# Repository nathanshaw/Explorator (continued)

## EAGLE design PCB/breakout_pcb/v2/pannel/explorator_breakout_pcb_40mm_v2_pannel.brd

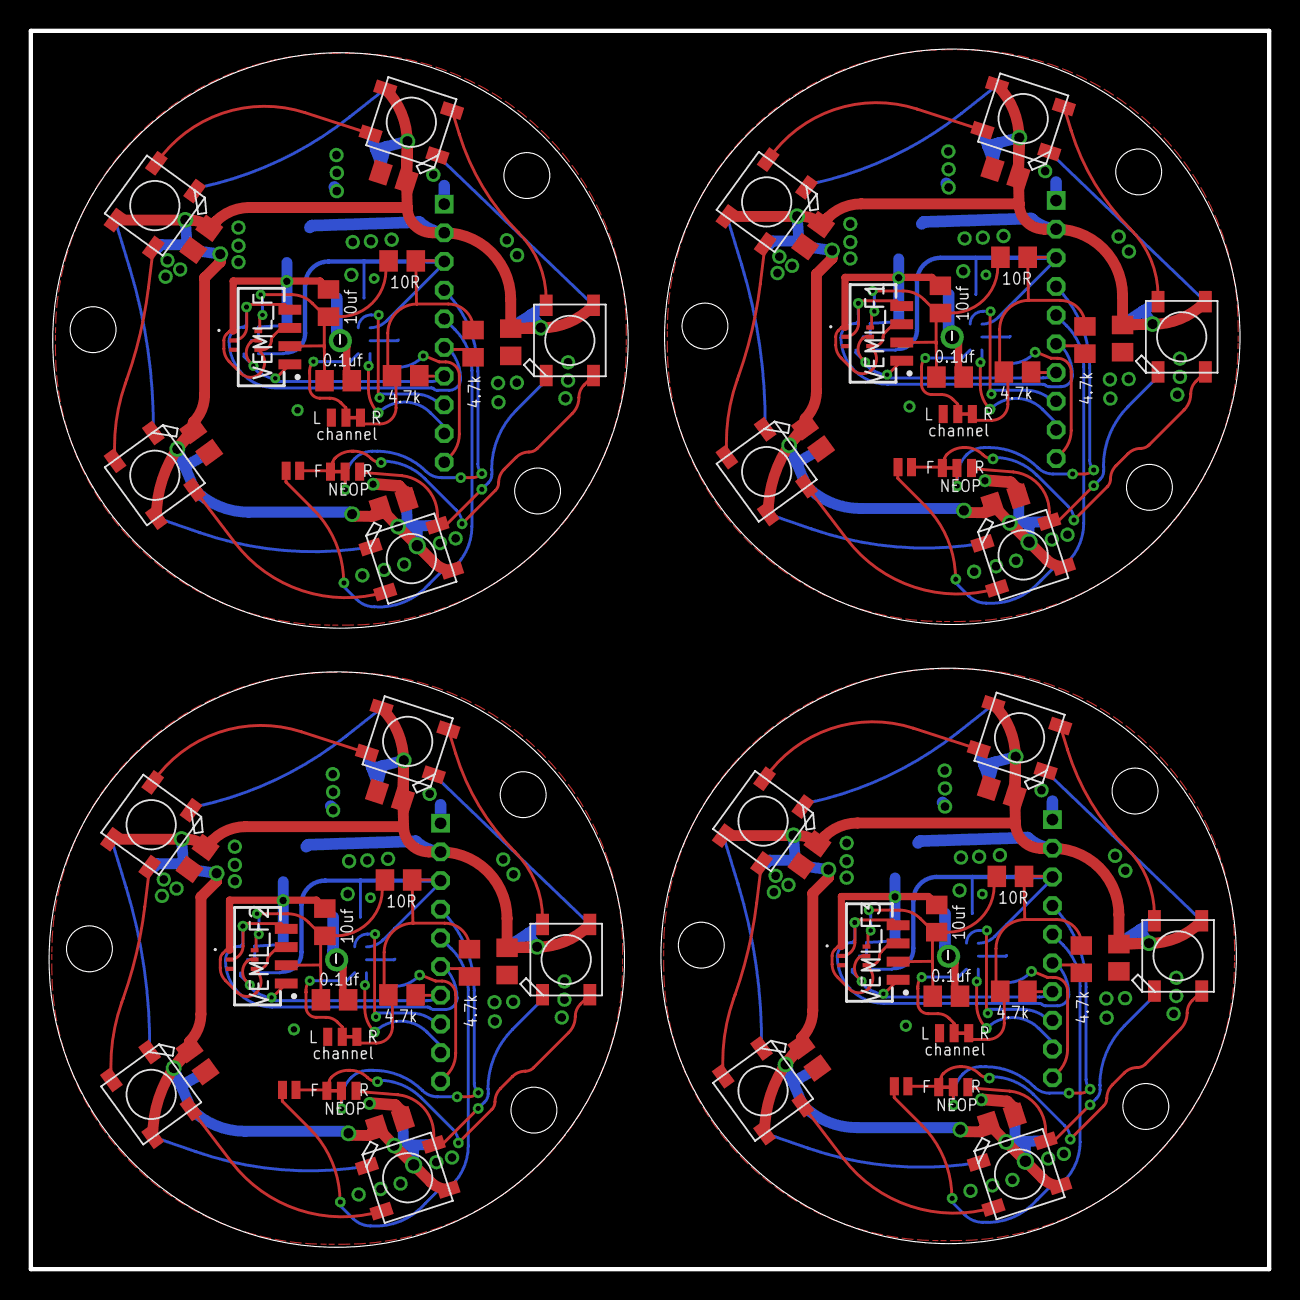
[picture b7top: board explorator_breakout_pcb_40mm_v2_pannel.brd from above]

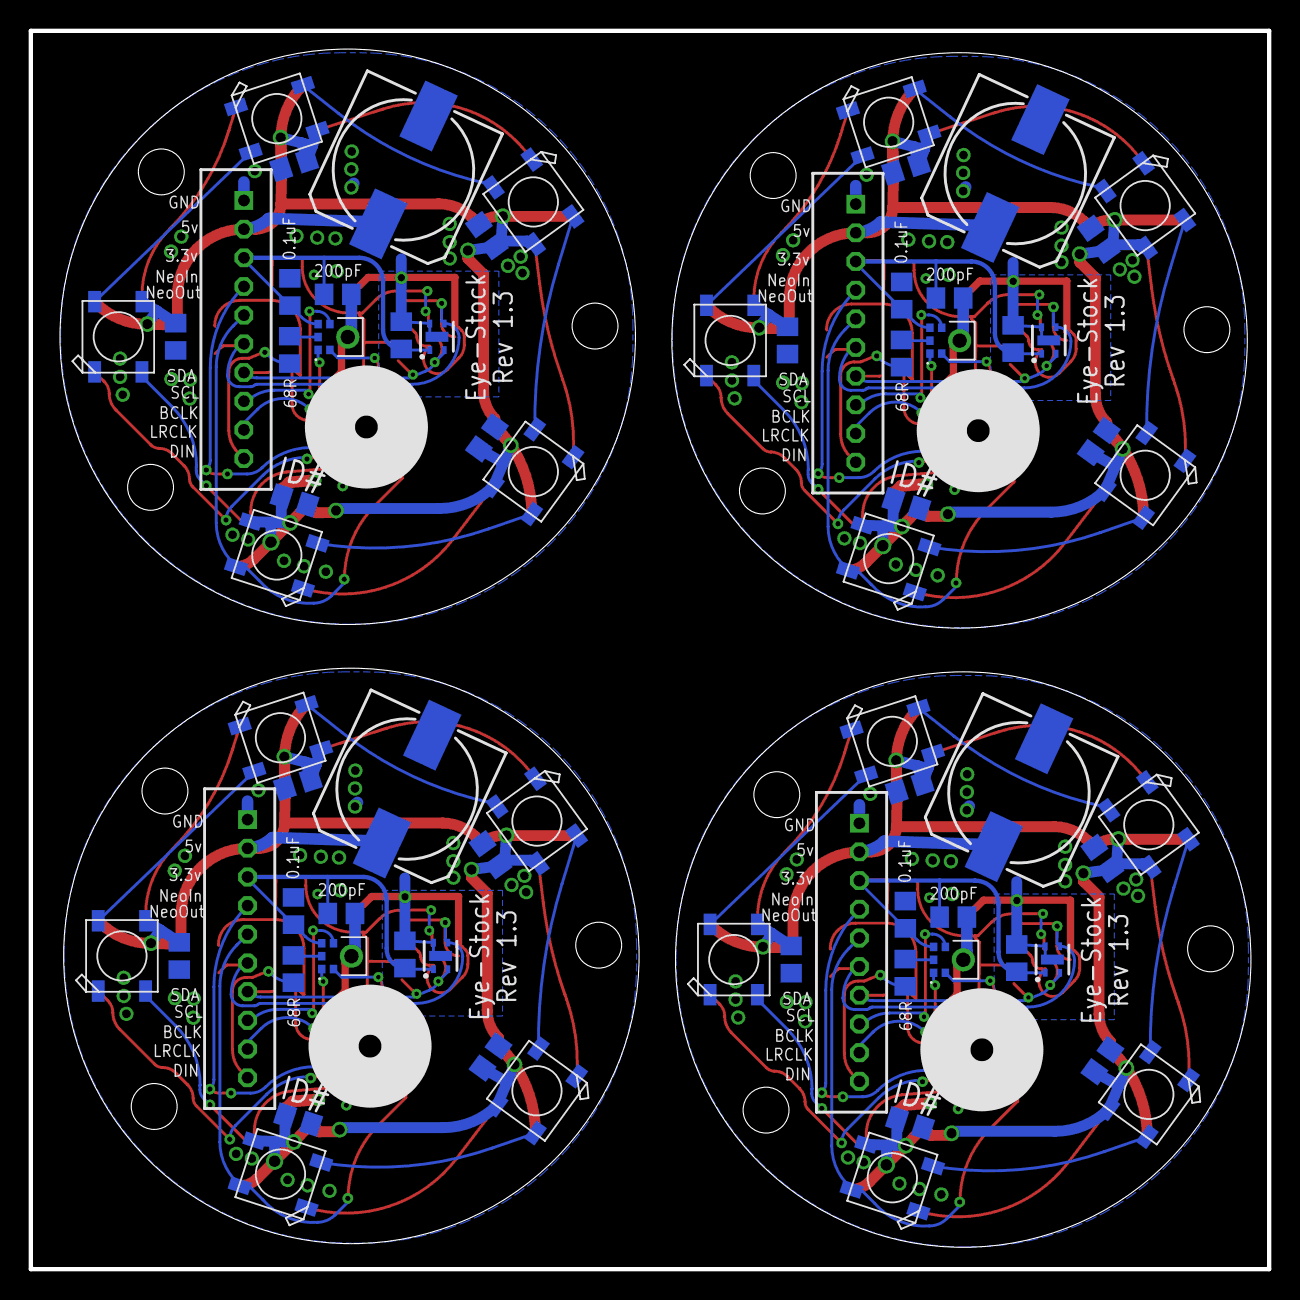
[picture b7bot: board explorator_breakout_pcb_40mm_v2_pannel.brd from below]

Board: 2 copper layers, 86.4 x 86.4 mm, 152 parts (72 on the bottom side), 92 nets.

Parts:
C1, C5, C13, C19: 0.1uf; C0805
C2, C7, C8, C11, C15, C17, C21, C23: 0.1uF; C0805
C3, C12, C18, C24: 1mF; 153CLV-1012
C4, C6, C14, C20: 10uf; C0805
C9, C10, C16, C22: 200pF; C0805
JP1, JP2, JP3, JP5, JP7, JP8, JP10, JP11: JUMPER-SMT-3POS_NC_ONE; SMT-JUMPER_3_1-NC_TRACE_NO-SILK
JP4, JP6, JP9, JP12: JUMPER-SMT-2POS; SMT-JUMPER_2_NO_NO-SILK
MK_REAR, MK_REAR1, MK_REAR2, MK_REAR3: SPH-IMPROVED; MIC_SPH0645LM4H-B_LARGER_RING
NC1, NC2, NC3, NC4, NC5, NC6, NC7, NC8, NC9, NC10, NC11, NC12, NC13, NC14, NC15, NC16, NC17, NC18, NC19, NC20, NC21, NC22, NC23, NC24, NC25, NC26, NC27, NC28, NC29, NC30, NC31, NC32, NC33, NC34, NC35, NC36, NC37, NC38, NC39, NC40: 0.1uf; C0805
NEO_01, NEO_02, NEO_03, NEO_04, NEO_05, NEO_06, NEO_07, NEO_08, NEO_09, NEO_10, NEO_11, NEO_12, NEO_13, NEO_14, NEO_15, NEO_16, NEO_17, NEO_18, NEO_19, NEO_20, NEO_21, NEO_22, NEO_23, NEO_24, NEO_25, NEO_26, NEO_27, NEO_28, NEO_29, NEO_30, NEO_31, NEO_32, NEO_33, NEO_34, NEO_35, NEO_36, NEO_37, NEO_38, NEO_39, NEO_40: WS2812; WS2812B
P1, P2, P3, P4: B10B-PH-K
R1, R3, R8, R12: 10R; R0805
R2, R4, R5, R6, R9, R10, R13, R14: 4.7k; R0805
R7, R11, R15, R16: 68R; R0805
U1, U3, U5, U7: SHTC3
U2, U4, U6, U8: VEML6030-GS15; VISHAY_VEML6030_2X2X0.87
VEML_F, VEML_F1, VEML_F2, VEML_F3: VEML7700-TT; VEML7700

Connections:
3.3V: C2.1, C8.1, C9.1, JP3.3, MK_REAR.5, P1.3, R3.2, R5.2, R6.2, U1.1
3.3V1: C7.1, C10.1, C11.1, JP5.3, MK_REAR1.5, P2.3, R1.2, R2.2, R4.2, U3.1
3.3V2: C15.1, C16.1, C17.1, JP8.3, MK_REAR2.5, P3.3, R8.2, R9.2, R10.2, U5.1
3.3V3: C21.1, C22.1, C23.1, JP11.3, MK_REAR3.5, P4.3, R12.2, R13.2, R14.2, U7.1
5V: C3.+, NC1.1, NC2.1, NC3.1, NC4.1, NC5.1, NC6.1, NC7.1, NC8.1, NC9.1, NC10.1, NEO_01.1-VDD, NEO_02.1-VDD, NEO_03.1-VDD, NEO_04.1-VDD, NEO_05.1-VDD, NEO_06.1-VDD, NEO_07.1-VDD, NEO_08.1-VDD, NEO_09.1-VDD, NEO_10.1-VDD, P1.2
5V1: C12.+, NC11.1, NC12.1, NC13.1, NC14.1, NC15.1, NC16.1, NC17.1, NC18.1, NC19.1, NC20.1, NEO_11.1-VDD, NEO_12.1-VDD, NEO_13.1-VDD, NEO_14.1-VDD, NEO_15.1-VDD, NEO_16.1-VDD, NEO_17.1-VDD, NEO_18.1-VDD, NEO_19.1-VDD, NEO_20.1-VDD, P2.2
5V2: C18.+, NC21.1, NC22.1, NC23.1, NC24.1, NC25.1, NC26.1, NC27.1, NC28.1, NC29.1, NC30.1, NEO_21.1-VDD, NEO_22.1-VDD, NEO_23.1-VDD, NEO_24.1-VDD, NEO_25.1-VDD, NEO_26.1-VDD, NEO_27.1-VDD, NEO_28.1-VDD, NEO_29.1-VDD, NEO_30.1-VDD, P3.2
5V3: C24.+, NC31.1, NC32.1, NC33.1, NC34.1, NC35.1, NC36.1, NC37.1, NC38.1, NC39.1, NC40.1, NEO_31.1-VDD, NEO_32.1-VDD, NEO_33.1-VDD, NEO_34.1-VDD, NEO_35.1-VDD, NEO_36.1-VDD, NEO_37.1-VDD, NEO_38.1-VDD, NEO_39.1-VDD, NEO_40.1-VDD, P4.2
BCLK: MK_REAR.4, P1.8
BCLK1: MK_REAR1.4, P2.8
BCLK2: MK_REAR2.4, P3.8
BCLK3: MK_REAR3.4, P4.8
DIN: P1.10, R15.2
DIN1: P2.10, R7.2
DIN2: P3.10, R11.2
DIN3: P4.10, R16.2
GND: C1.2, C2.2, C3.-, C4.2, C8.2, C9.2, JP3.1, MK_REAR.P$1, NC1.2, NC2.2, NC3.2, NC4.2, NC5.2, NC6.2, NC7.2, NC8.2, NC9.2, NC10.2, NEO_01.3-GND, NEO_02.3-GND, NEO_03.3-GND, NEO_04.3-GND, NEO_05.3-GND, NEO_06.3-GND, NEO_07.3-GND, NEO_08.3-GND, NEO_09.3-GND, NEO_10.3-GND, P1.1, U1.4, U1.5, U2.1, U2.4, VEML_F.3
GND1: C5.2, C6.2, C7.2, C10.2, C11.2, C12.-, JP5.1, MK_REAR1.P$1, NC11.2, NC12.2, NC13.2, NC14.2, NC15.2, NC16.2, NC17.2, NC18.2, NC19.2, NC20.2, NEO_11.3-GND, NEO_12.3-GND, NEO_13.3-GND, NEO_14.3-GND, NEO_15.3-GND, NEO_16.3-GND, NEO_17.3-GND, NEO_18.3-GND, NEO_19.3-GND, NEO_20.3-GND, P2.1, U3.4, U3.5, U4.1, U4.4, VEML_F1.3
GND2: C13.2, C14.2, C15.2, C16.2, C17.2, C18.-, JP8.1, MK_REAR2.P$1, NC21.2, NC22.2, NC23.2, NC24.2, NC25.2, NC26.2, NC27.2, NC28.2, NC29.2, NC30.2, NEO_21.3-GND, NEO_22.3-GND, NEO_23.3-GND, NEO_24.3-GND, NEO_25.3-GND, NEO_26.3-GND, NEO_27.3-GND, NEO_28.3-GND, NEO_29.3-GND, NEO_30.3-GND, P3.1, U5.4, U5.5, U6.1, U6.4, VEML_F2.3
GND3: C19.2, C20.2, C21.2, C22.2, C23.2, C24.-, JP11.1, MK_REAR3.P$1, NC31.2, NC32.2, NC33.2, NC34.2, NC35.2, NC36.2, NC37.2, NC38.2, NC39.2, NC40.2, NEO_31.3-GND, NEO_32.3-GND, NEO_33.3-GND, NEO_34.3-GND, NEO_35.3-GND, NEO_36.3-GND, NEO_37.3-GND, NEO_38.3-GND, NEO_39.3-GND, NEO_40.3-GND, P4.1, U7.4, U7.5, U8.1, U8.4, VEML_F3.3
LRCLK: MK_REAR.1, P1.9
LRCLK1: MK_REAR1.1, P2.9
LRCLK2: MK_REAR2.1, P3.9
LRCLK3: MK_REAR3.1, P4.9
unnamed: C1.1, C4.1, R3.1, U2.6, VEML_F.2
unnamed: JP1.1, NEO_05.2-DOUT, NEO_06.4-DIN
unnamed: NEO_11.2-DOUT, NEO_12.4-DIN
unnamed: NEO_02.2-DOUT, NEO_03.4-DIN
unnamed: NEO_09.2-DOUT, NEO_10.4-DIN
unnamed: JP3.2, MK_REAR.2
unnamed: NEO_07.2-DOUT, NEO_08.4-DIN
unnamed: NEO_04.2-DOUT, NEO_05.4-DIN
unnamed: NEO_08.2-DOUT, NEO_09.4-DIN
unnamed: NEO_03.2-DOUT, NEO_04.4-DIN
unnamed: NEO_14.2-DOUT, NEO_15.4-DIN
unnamed: C5.1, C6.1, R1.1, U4.6, VEML_F1.2
unnamed: NEO_11.4-DIN, NEO_15.2-DOUT
unnamed: MK_REAR1.6, R7.1
unnamed: JP5.2, MK_REAR1.2
unnamed: NEO_16.2-DOUT, NEO_17.4-DIN
unnamed: MK_REAR.6, R15.1
unnamed: NEO_19.2-DOUT, NEO_20.4-DIN
unnamed: NEO_16.4-DIN, NEO_20.2-DOUT
unnamed: JP2.1, NEO_12.2-DOUT, NEO_18.4-DIN
unnamed: NEO_21.2-DOUT, NEO_22.4-DIN
unnamed: NEO_24.2-DOUT, NEO_25.4-DIN
unnamed: C13.1, C14.1, R8.1, U6.6, VEML_F2.2
unnamed: NEO_21.4-DIN, NEO_25.2-DOUT
unnamed: MK_REAR2.6, R11.1
unnamed: JP8.2, MK_REAR2.2
unnamed: NEO_26.2-DOUT, NEO_27.4-DIN
unnamed: NEO_29.2-DOUT, NEO_30.4-DIN
unnamed: NEO_26.4-DIN, NEO_30.2-DOUT
unnamed: JP7.1, NEO_22.2-DOUT, NEO_28.4-DIN
unnamed: NEO_31.2-DOUT, NEO_32.4-DIN
unnamed: NEO_34.2-DOUT, NEO_35.4-DIN
unnamed: C19.1, C20.1, R12.1, U8.6, VEML_F3.2
unnamed: NEO_31.4-DIN, NEO_35.2-DOUT
unnamed: MK_REAR3.6, R16.1
unnamed: JP11.2, MK_REAR3.2
unnamed: NEO_36.2-DOUT, NEO_37.4-DIN
unnamed: NEO_39.2-DOUT, NEO_40.4-DIN
unnamed: NEO_36.4-DIN, NEO_40.2-DOUT
unnamed: JP10.1, NEO_32.2-DOUT, NEO_38.4-DIN
NEOP_IN: JP1.3, JP4.2, NEO_01.4-DIN
NEOP_IN1: JP2.3, JP6.2, NEO_13.4-DIN
NEOP_IN2: JP7.3, JP9.2, NEO_23.4-DIN
NEOP_IN3: JP10.3, JP12.2, NEO_33.4-DIN
NEOP_OUT: JP4.1, NEO_10.2-DOUT, P1.5
NEOP_OUT1: JP6.1, NEO_17.2-DOUT, P2.5
NEOP_OUT2: JP9.1, NEO_27.2-DOUT, P3.5
NEOP_OUT3: JP12.1, NEO_37.2-DOUT, P4.5
NEO_P1: NEO_01.2-DOUT, NEO_02.4-DIN
NEO_P2: NEO_06.2-DOUT, NEO_07.4-DIN
NEO_P3: NEO_13.2-DOUT, NEO_14.4-DIN
NEO_P4: NEO_18.2-DOUT, NEO_19.4-DIN
NEO_P5: NEO_23.2-DOUT, NEO_24.4-DIN
NEO_P6: NEO_28.2-DOUT, NEO_29.4-DIN
NEO_P7: NEO_33.2-DOUT, NEO_34.4-DIN
NEO_P8: NEO_38.2-DOUT, NEO_39.4-DIN
NIN: JP1.2, P1.4
NIN1: JP2.2, P2.4
NIN2: JP7.2, P3.4
NIN3: JP10.2, P4.4
SCL0: P1.7, R5.1, U1.2, U2.5, VEML_F.1
SCL1: P2.7, R4.1, U3.2, U4.5, VEML_F1.1
SCL2: P3.7, R10.1, U5.2, U6.5, VEML_F2.1
SCL3: P4.7, R14.1, U7.2, U8.5, VEML_F3.1
SDA0: P1.6, R6.1, U1.3, U2.2, VEML_F.4
SDA1: P2.6, R2.1, U3.3, U4.2, VEML_F1.4
SDA2: P3.6, R9.1, U5.3, U6.2, VEML_F2.4
SDA3: P4.6, R13.1, U7.3, U8.2, VEML_F3.4

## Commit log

2022-09-17 added layout and schematic files
2023-03-21 added parts_list, gerbers, and images for the 18500 pack PCB
2023-03-21 revised .gitignore to better handle EAGLE files and the .vscode folder
2023-03-21 updated the breakout_pcb folder to only include the most recent PCB revision, added a README for the board, updated the parts_list, and generated gerbers
2023-03-21 added README.md, CAMOutputes, parts_list.txt, and BOM*.csv files for the 18650 battery pack
2023-03-21 added schematic and layout .png files for the battery packs and breakout pcb, added BOM files for battery packs and breakout pcb, added in the high-level .cam file used to generate gerbers for the pr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
2023-03-21 updated the battery packs to now contain all the necisary information
2023-03-21 updated the breakout_pcb folder to contain all the same information as the batter packs, also fixed a few bugs and typos in the README.md files
2023-03-21 renamed several files and folers, updated the breakout PCB and the large mainboard PCBs to contain all info except for proper README.md files
2023-03-21 oops, accidently deleted instead of moving some boards earlier
2023-03-21 updated the mainboard's with the new information found in other folders including net_lists, parts_lists, pin_lists, and such
